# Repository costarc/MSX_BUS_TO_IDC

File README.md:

# MSX_BUS_TO_IDC

V1.0

This MSX interface exposes the MSX BUS via an IDC connector.
The IDC pinout layout matches the Altera DE1 Development board.

There is no voltage level conversion, therefore this interface must be used only with MSX FPGA clones
because they already operate at 3.3v level.

Do ont use this interface to connect a real MSX (which operates with a 5V bus) to the Altra DE1.

The pull-ups resistors are optional. They may be installed if you determine that your project requires pull-ups in those lines.

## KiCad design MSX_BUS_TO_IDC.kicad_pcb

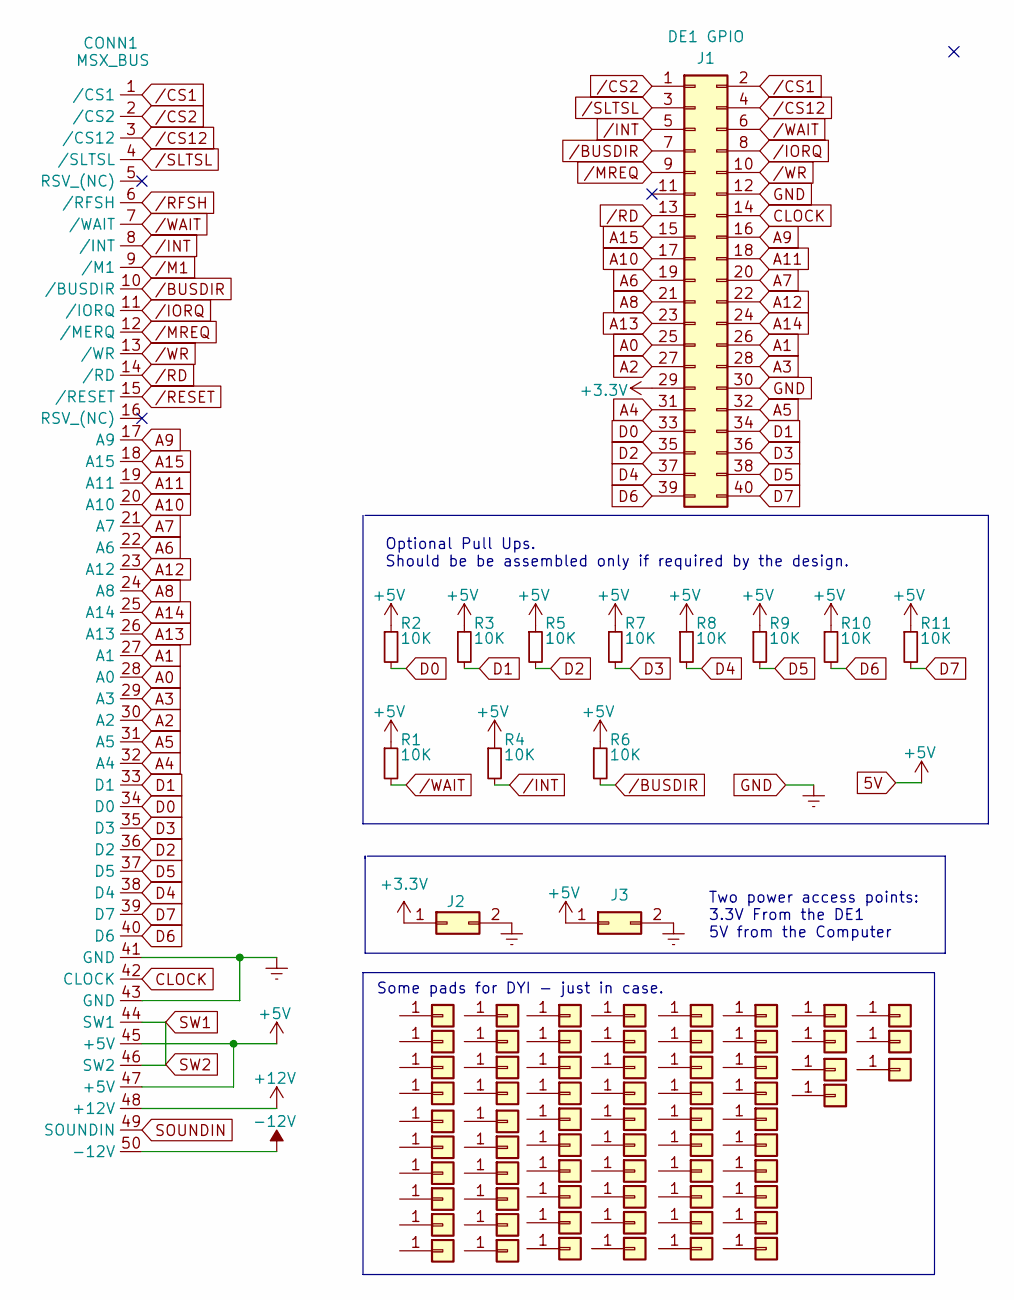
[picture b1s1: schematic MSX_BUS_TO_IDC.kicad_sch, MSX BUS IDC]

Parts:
CONN1: MSX_BUS; MSX_CART
J1: DE1 GPIO; IDC-Header_2x20_P2.54mm_Vertical
J2, J3: Conn_02x01; PinHeader_1x02_P2.54mm_Vertical
J4, J5, J6, J7, J8, J9, J10, J11, J12, J13, J14, J15, J16, J17, J18, J19, J20, J21, J22, J23, J24, J25, J26, J27, J28, J29, J30, J31, J32, J33, J34, J35, J36, J37, J38, J39, J40, J41, J42, J43, J44, J45, J46, J47, J48, J49, J50, J51, J52, J53, J54, J55, J56, J57, J58, J59, J60, J61, J62, J63, J64, J65, J66, J67, J68, J69, J70: Conn_01x01; TestPoint_THTPad_2.0x2.0mm_Drill1.0mm
R1, R2, R3, R4, R5, R6, R7, R8, R9, R10, R11: 10K; R_Axial_DIN0207_L6.3mm_D2.5mm_P7.62mm_Horizontal

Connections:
5V: CONN1.45 (+5V), CONN1.47 (+5V), J3.1, R1.1, R2.1, R3.1, R4.1, R5.1, R6.1, R7.1, R8.1, R9.1, R10.1, R11.1
+3.3V: J1.29, J2.1
+12V: CONN1.48 (+12V)
-12V: CONN1.50 (-12V)
A0: CONN1.28 (A0), J1.25
A1: CONN1.27 (A1), J1.26
A2: CONN1.30 (A2), J1.27
A3: CONN1.29 (A3), J1.28
A4: CONN1.32 (A4), J1.31
A5: CONN1.31 (A5), J1.32
A6: CONN1.22 (A6), J1.19
A7: CONN1.21 (A7), J1.20
A8: CONN1.24 (A8), J1.21
A9: CONN1.17 (A9), J1.16
A10: CONN1.20 (A10), J1.17
A11: CONN1.19 (A11), J1.18
A12: CONN1.23 (A12), J1.22
A13: CONN1.26 (A13), J1.23
A14: CONN1.25 (A14), J1.24
A15: CONN1.18 (A15), J1.15
CLOCK: CONN1.42 (CLOCK), J1.14
D0: CONN1.34 (D0), J1.33, R2.2
D1: CONN1.33 (D1), J1.34, R3.2
D2: CONN1.36 (D2), J1.35, R5.2
D3: CONN1.35 (D3), J1.36, R7.2
D4: CONN1.38 (D4), J1.37, R8.2
D5: CONN1.37 (D5), J1.38, R9.2
D6: CONN1.40 (D6), J1.39, R10.2
D7: CONN1.39 (D7), J1.40, R11.2
GND: CONN1.41 (GND), CONN1.43 (GND), J1.12, J1.30, J2.2, J3.2
SOUNDIN: CONN1.49 (SOUNDIN)
SW1: CONN1.44 (SW1), CONN1.46 (SW2)
/BUSDIR: CONN1.10 (/BUSDIR), J1.7, R6.2
/CS1: CONN1.1 (/CS1), J1.2
/CS2: CONN1.2 (/CS2), J1.1
/CS12: CONN1.3 (/CS12), J1.4
/INT: CONN1.8 (/INT), J1.5, R4.2
/IORQ: CONN1.11 (/IORQ), J1.8
/M1: CONN1.9 (/M1)
/MREQ: CONN1.12 (/MERQ), J1.9
/RD: CONN1.14 (/RD), J1.13
/RESET: CONN1.15 (/RESET)
/RFSH: CONN1.6 (/RFSH)
/SLTSL: CONN1.4 (/SLTSL), J1.3
/WAIT: CONN1.7 (/WAIT), J1.6, R1.2
/WR: CONN1.13 (/WR), J1.10

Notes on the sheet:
Two power access points: 3.3V From the DE1 5V from the Computer
Some pads for DYI - just in case.
Optional Pull Ups. Should be be assembled only if required by the design.

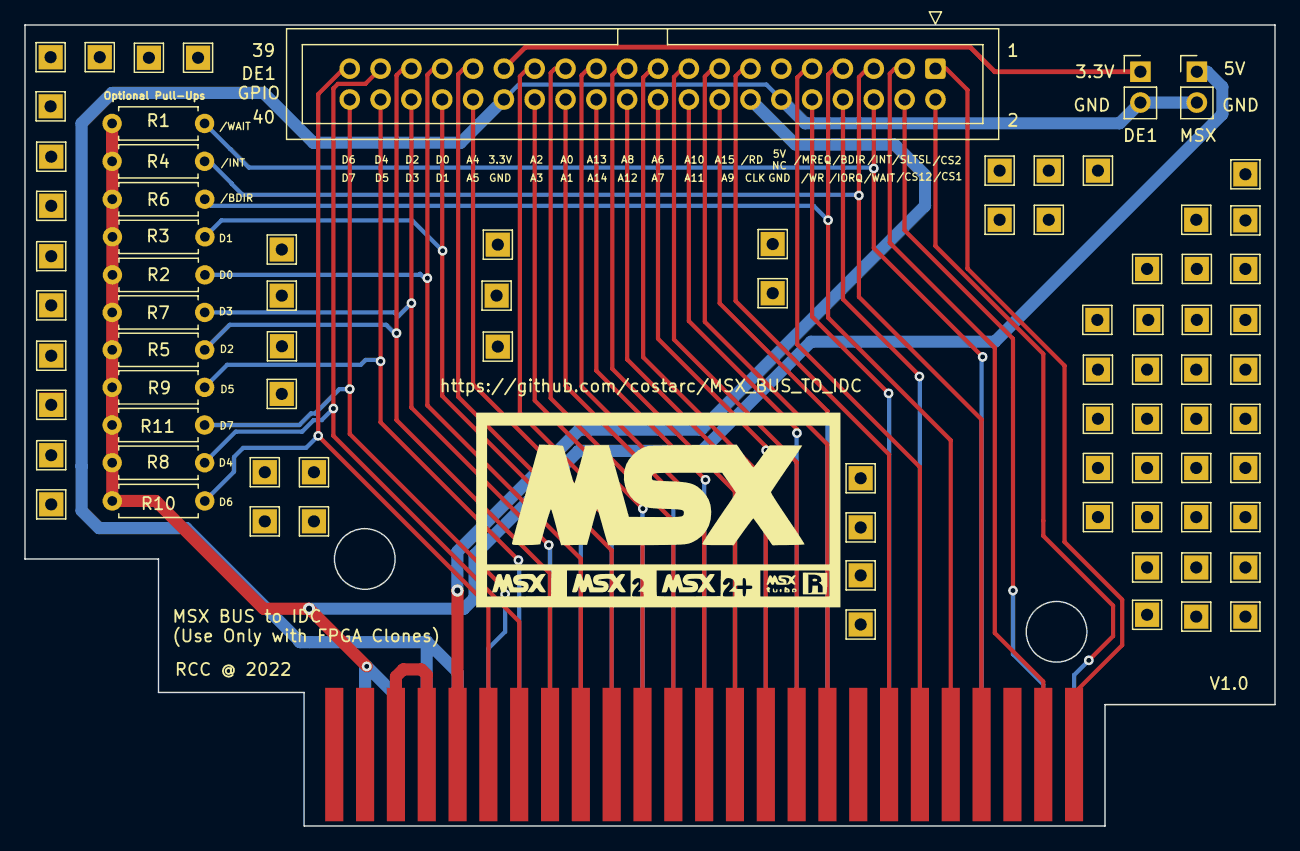
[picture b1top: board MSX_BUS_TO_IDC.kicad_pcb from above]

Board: 2 copper layers, 103.0 x 66.0 mm, 82 parts (0 on the bottom side), 40 nets.

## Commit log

2022-12-19 Fabrication files added
2022-12-19 Adjusted footprints for resistors
2023-01-17 Added Gerber files
